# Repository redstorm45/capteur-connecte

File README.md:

# Introduction

Code arduino et python du projet de capteur connecté.<br/>
Il est fait pour utilisation avec un ESP8266 (ESP-01), mais est sûrement utilisable pour d'autres modèles d'ESP.<br/>
Il est aussi fait pour utiliser un capteur Dallas DS18B20, communiquant avec le protocole One-Wire.

## Librairies

Le programme utilise les librairies suivantes:
- [DallasTemperature](https://github.com/milesburton/Arduino-Temperature-Control-Library)
- [NTPClient](https://github.com/arduino-libraries/NTPClient)
- OneWire
- [PubSubClient](https://github.com/knolleary/pubsubclient)

# Vue générale

## Architecture des transferts de données

Les données provennant du capteur sont captées par le programme à travers la bibliothèque OneWire, et converties en nombre à virgule flottante par la bibliothèque DallasTemperature.<br/>
À la réception, les données sont datés à l'aide de la bibliothèque NTPClient, et stockées dans un tampon temporaire avant envoi.<br/>
À interval fixe, le programme tente de vider tout le tampon de mesures, par des envois successifs à l'aide de MQTT, par la bibliothèque PubSubClient. Néanmoins, afin de ne pas trop impacter les prises de mesures, il ne s'effectue qu'un envoi par boucle principale, alors que cette même boucle vérifie à chaque fois s'il faut prendre une mesure, et fait fonctionner la pile TCP de l'ESP8266 au besoin.

## Modes de fonctionnement

## Configuration

En haut du programme sont définies les différentes constantes et variables utilisées pour le projet,
ainsi que les options de configuration.

### Constantes

Ces constantes permettent de définir les différents délais ainsi que les interfaces du programme, afin de pouvoir le régler selon l'application voulue.

| Nom                        | Unité | Fonction                                                                                      |
|----------------------------|-------|-----------------------------------------------------------------------------------------------|
| PIN_CAPTEUR                | N/A   | Identifiant du pin sur lequel est connecté le capteur Dallas DS18B20                          |
| DELAI\_MESURE              | ms    | Délai entre chaque mesure en fonctionnement normal                                            |
| DELAI\_MESURE\_ECRASANT    | ms    | Délai entre chaque mesure en fonctionnement dégradé                                           |
| DELAI\_MESURE\_CONVERSION  | ms    | Délai permettant au capteur de réaliser sa mesure, avant de la lui demander                   |
| DELAI_ENVOI                | ms    | Délai entre chaque tentative d'envoi des données                                              |
| DELAI_NTP                  | ms    | Délai entre chaque synchronisation avec le serveur NTP                                        |
| OFFSET_NTP                 | s     | Décalage horaire entre l'heure NTP (UTC) et le fuseau actuel                                  |
| LONGUEUR_BUFFER (buffer.h) | N/A   | Défini la taille du buffer à utiliser, à choisir suivant la place restante pour les variables |

### Fonctionnement

Ces constantes permettent d'appliquer une compilation différente au programme, donc un fonctionnement différent.

| Nom         | Fonction (si définie)                                                                                                           |
|-------------|---------------------------------------------------------------------------------------------------------------------------------|
| DEBUG       | Ajoute des envois de messages par le port série sur divers événements                                                           |
| NTP_SERVER  | Utilise un serveur NTP, plutôt que d'attendre l'heure sous la forme d'un timestamp transmis par MQTT sur le channel "timestamp" |

# Programmation sur un ESP8266 (ESP-01)

## Position des pins

Voici l'arrangement des pins sur un ESP-01, vu de dessus (pins en dessous), avec l'antenne wi-fi sur la gauche.

|       |       |
|-------|-------|
| RX    | VCC   |
| GPIO0 | RST   |
| GPIO2 | CH_PD |
| GND   | TX    |

## Connexion

On connecte les pins suivants sur un convertisseur USB <> Port série quelconque. Un Arduino peut remplir cette fonction, sans avoir à utiliser le sketch "Arduino as ISP", en fixant son pin de reset à la masse. Il ne semble pas nécessaire d'utiliser un convertisseur de niveau logique pour éviter d'abîmer la carte.

| Pin ESP8266   | Connecté à                                             |
|---------------|--------------------------------------------------------|
| RX            | TX du convertisseur série                              |
| GPIO0         | pulldown pour programmer, pullup pour lancement normal |
| GPIO2         | pullup + capteur DS18B20                               |
| GND           | Masse                                                  |
| VCC           | Alimentation +3.3V                                     |
| RST           | pullup                                                 |
| CH_PD         | pullup                                                 |
| TX            | RX du convertisseur série                              |

## Envoi du programme

Avant d'envoyer, on effectue une mise à la masse du pin de reset (RST), pour s'assurer que l'ESP n'est pas en train d'executer un programme.
On s'assure aussi d'avoir choisi la carte "Generic ESP8266 Module" dans l'IDE Arduino, pour lequel il faut avoir installé les bibliothèques de programmation pour l'ESP dans le gestionnaire de cartes. On vérifie enfin que le port série choisi est valide. Finalement, on peut envoyer le programme à l'aide du bouton "téléverser".

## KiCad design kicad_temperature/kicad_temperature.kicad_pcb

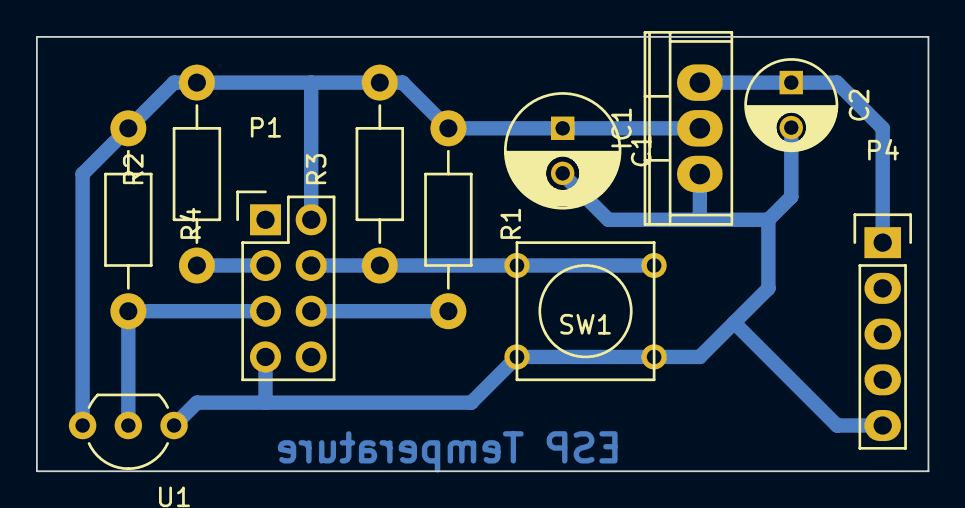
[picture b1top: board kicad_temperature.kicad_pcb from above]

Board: 2 copper layers, 49.5 x 24.1 mm, 11 parts (0 on the bottom side), 7 nets.

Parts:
C1: 100µF; C_Radial_D6.3_L11.2_P2.5
C2: 10µF; C_Radial_D5_L11_P2.5
IC1: LM1117; TO-220
P1: CONN_02X04; Pin_Header_Straight_2x04
P4: CONN_01X05; Pin_Header_Straight_1x05
R1, R2, R3: 10k; Resistor_Horizontal_RM10mm
R4: 4.7k; Resistor_Horizontal_RM10mm
SW1: SW_PUSH; SW_PUSH_SMALL
U1: DS18B20; TO-92_Inline_Wide

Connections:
/CH_PD: P1.6, R1.2
/GPIO0: P1.3, R2.1
/GPIO2: P1.5, R4.2, U1.2
/RST: P1.4, R3.1, SW1.2
/VCC: C1.1, IC1.2, P1.2, R1.1, R2.2, R3.2, R4.1, U1.3
GND: C1.2, C2.2, IC1.1, P1.7, P4.5, SW1.1, U1.1
unnamed: C2.1, IC1.3, P4.1

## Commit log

2017-12-06 Ajout d'une base de code Arduino
2017-12-07 Reorganisateur de données en un tableau de bytes
2017-12-07 Buffer
    Classe du buffer, premier jet
2017-12-08 pop
    Allow to pop data
2017-12-15 Nettoyage
2017-12-16 Nouveau buffer
2017-12-16 Génere des publications MQTT
2017-12-16 Fix du buffer
2017-12-16 Programme fonctionnel
2017-12-17 Fix bufer
2018-01-18 Ajout du fonctionnement degrade
2018-02-14 Passage en qos 2
2018-02-14 Ajout du mode debug
2018-02-20 Fix fin du buffer
2018-02-20 Changement de lib MQTT
2018-02-20 N'utilise plus le NTP, car indisponible en test :-(
2018-03-26 Séparation des modes de fonctionnement pour le NTP ou le timestamp par MQTT
2018-03-26 mise à jour du README
2018-03-26 Fix README
2018-03-26 Fix(2) README
2018-05-15 Circuit du capteur de temperature
2018-05-15 Modification des co,stantes de temps
2018-05-15 Modèles 3D du capteur de température
